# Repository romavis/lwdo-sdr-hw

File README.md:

# What

**LWDO-SDR** is an experimental device for wide-band LF/VLF radio reception and using LF/VLF signals for precise timekeeping and generic DSP/SDR research purposes.

The name LWDO-SDR *(**l**ong-**w**ave **d**isciplined **o**scillator with **s**oftware **d**efined **r**adio)* is a moniker aking to a widely-used *GPSDO* term, but instead of GPS we use signals transmitted within long wave radio band, and SDR for signal processing.

# Goals

LWDO-SDR is built upon following ideas:
- Wide dynamic range capture of the whole LF/VLF radio spectrum (up to 500 KHz)
  - Simultaneous reception of any number of stations
  - Exposing it as a WebSDR (for the fun of it?)
- Precise built-in VCTCXO oscillator
  - Generates tightly controlled ADC sample clock that allows for SDR processing using large-time-constant averaging
  - Digitally-controlled (via 16 bit DAC), and can be disciplined by:
    - External 1 PPS or 1,2,5,10MHz reference (via DPLL)
    - Received radio signals
- Synchronous capture from multiple antennas (up to 4)
  - Experiments with urban noise suppression SDR algorithms 
  - Directional reception (using e.g. two or three loop antennas)
- Raw data streaming over USB High Speed interface, processing on the USB host device (PC, RaspberryPi, etc.)
  - Because we don't want to be limited by computing power of an embedded MCU or DSP
- Single PCB, two form-factors:
  - Standalone, USB bus-powered - for ease of use and portability (uses Hammond 1455P1601 case)
  - Embedded, self-powered - for use within e.g. a standalone clock source unit within the home lab.

Some signals that can be received by LWDO-SDR are:
- [DCF77 - 77.5KHz](https://en.wikipedia.org/wiki/DCF77)
- [MSF - 60 KHz](https://en.wikipedia.org/wiki/Time_from_NPL_(MSF))
- [RBU - 66.67 KHz](https://en.wikipedia.org/wiki/RBU_(radio_station))
- [TDF - 162 KHz](https://en.wikipedia.org/wiki/ALS162_time_signal)
- [Loran - 100 KHz](https://en.wikipedia.org/wiki/Loran-C)

# Drawings

PDF renders:
- [Schematic](./doc/schematic-rev1.0.pdf)
- [PCB visualisation](./doc/pcb-rev1.0.pdf)

Curious ones are kindly asked to look into the original KiCad 6.0.4 CAD files, which include full PCB drawings and BOM information.

Photo of assembled board can be seen [here](./doc/pcb-photo-rev1.0.jpg).

# HW description

### FPGA

The core of the LWDO-SDR is a low-end FPGA - *ICE40HX4K-TQ144* - that has:
- 3520x 4-input LUT, 1 FF logic cells (7680x with Yosys toolchain)
- 20x 4kbit dual-port block RAM cells (32x with Yosys)
- 2x PLLs
- DDR IO cells
- No hardware multipliers
- Typically achievable clock rates of 40~100MHz (depending on the design)

This FPGA has been chosen for its price and hobbyist-friendliness: TQFP144 can be soldered by hand and allows using 2-layer PCB. However, it is rather small so e.g. it may not be possible to use any kind of softCPU there (remains to be seen..). Any kind of sophisticated DSP is also out of the question, since there are no hardware multipliers.

The bitstream together with any extra user data is stored within 2 MByte QSPI flash - *W25Q16JV*.

FPGA is also connected to a 10 ns 512 KByte SRAM with 16 bit data bus - *IS61WV25616FBLL-10TLI*. At this moment it is not clear how much useful the SRAM may be, given overall FPGA footprint constraints.

### USB

USB 2.0 High Speed is implemented by FTDI FT2232H chip. It has two external channels, allocated as follows:
- Channel A - synchronous FIFO - allows data streaming from/to FPGA up to 40 MByte/s over USB bulk endpoints
- Channel B - MPSSE (SPI) + GPIO - to program bitstream SPI flash and handle CRESET, CDONE, and a pair of extra GPIO-like signals from FPGA (similar to how it's done on the [iCEstick](https://www.latticesemi.com/icestick). Available only when channel A is not in use.

### RF front-end

The board features four input channels for RF signals. All channels are the same:
1. 50 ohm DC-terminated SMA connector.
2. SD12C TVS ESD / overvoltage suppressor.
3. 2nd (3rd) order LC LPF (-3dB cutoff circa 530 KHz, rolloff 12 dB/oct).
4. Schottky diode overvoltage protection.
5. THS4521 fully-differential amplifier, performing unbalanced-balanced conversion and connected as a 2nd order LPF (-3dB cutoff circa 460 KHz, rolloff 12 dB/oct).
6. Passive RC LPF providing tank capacitance for driving the ADC (-3dB cutoff circa 1 MHz, rolloff 6 dB/oct)

### ADC

Board uses two [AD7357](https://www.analog.com/media/en/technical-documentation/data-sheets/AD7357.pdf), which is a 2-ch simulatenous-sampling 4.2 MSPS 14 bit SAR ADC. The output from each ADC is 2-bit serial bus. At a max sampling rate of 4.2 MSPS this ADC requires serial clock circa 80 MHz, which is provided by the FPGA.

**Note** to achieve timing closure for FPGA-ADC interface, taking into account propagation delays, setup times of ICE40HX IO cells, and especially AD7357 data valid delay (up to 9 ns), the generated clock is resampled on the FPGA pin:
- ICE40 outputs clock on the SCLK line (pin 15 or 20).
- ICE40 samples SCLK line via the input buffer of pin 20, and feeds that clock to the global clock net.
Compared to simply driving internal clock to the pin, this allows to take "global clock net -> pin output" delay (circa 2.5 ns) out of the timing equation.

### Clock source

[DOT050V-020.0M](http://www.conwin.com/datasheets/tx/tx395.pdf) VCTCXO from Connor-Winfield provides master 20 MHz clock for the FPGA, from which all the other clocks are generated using on-die PLLs.
DOT050V is a highly stable precision oscillator. Notable specs are:
- Factory frequency calibration: ±1 ppm
- Stability vs temperature 0~70 °C: ±50 **ppb**
- Stability vs load, supply voltage: ±20 ppb
- Aging over first year: ±300 ppb
- Voltage control frequency pulling range: at least ±10 ppm
- Comes in a standard 9x14mm SMT package

If needed, DOT050V can be easily replaced by some other, potentially cheaper, 3.3V VCTCXO or VCXO directly or through a simple adapter PCB (or DIY-style: some Kynar wire and hot glue). LWDO-SDR contains buffering circuitry that can accept oscillators with both square wave and (clipped) sine wave output.

The oscillator is voltage-controlled through by means of:
- 16-bit SPI DAC [DAC8551](https://www.ti.com/lit/ds/symlink/dac8551.pdf) driven by SPI master implemented on FPGA.
- DAC Vref provided by [MCP1501](https://ww1.microchip.com/downloads/en/DeviceDoc/20005474E.pdf), powered from filtered, unregulated 5V rail. 
- 1st order passive RC LPF (-3dB cutoff circa 160 Hz).
- Non-inverting buffer using [NCS325](www.onsemi.com/pub/Collateral/NCS325-D.PDF) rail-to-rail low-drift low-offset precision OpAmp.

### External clock input and output

There are two extra SMA connectors: one is for external clock input, one is for clock output from the board.

Clock output provides 1 Vpkpk 50 ohm terminated square wave output, AC or DC coupled (controlled by jumper). Output clock may come from one of two sources:
1. Dedicated FPGA pin.
2. 20 MHz master clock from VCTCXO.
The source is selected via a hardware LVCMOS multiplexer chip, controlled by the FPGA.

External clock input is 50 ohm terminated (above ~3MHz), AC or DC coupled. It is buffered and squared by a chain of unbuffered and buffered LVCMOS inverters, and fed to a dedicated FPGA pin.

**NOTE** clock input circuitry depicted on the schematic is sub-optimal. See "Errata" section below.

### External I/O

To allow LWDO-SDR PCB to be embedded, there's a 20-pin IDC ribbon cable connector which provides:
- 8 bit I/O bus connected to the FPGA:
  - Buffered via unidirectional 74AVC4T245 level translators.
  - Direction control for I/O lines is manual, by soldering/desoldering bridge resistors onto PCB.
  - Wired to a ribbon cable in G-S-G order, impedance-matched to a standard 1.27mm-pitch cable.
- External VDDIO supply for the level translators.
- External 5V supply for powering up the board (instead of using USB VBUS).

### LEDs

Board has 6 red/green bi-LEDs [WP130WCP/2EGW](https://www.kingbrightusa.com/images/catalog/SPEC/WP130WCP-2EGW.pdf):
- 4 for monitoring input status (located next to the input connectors)
- 1 for monitoring system status (located next to the USB)
- 1 hard-wired as a green power LED (located next to the USB)

### PCB

The board itself is 2-layer, designed to be manufacturable by [Eurocircuits](https://www.eurocircuits.com/) PCB Proto service according to Class 5C (0.175mm track, 0.25mm annular ring, 0.25mm smallest final hole).

# Software

The testing of rev 1.0 board is, as of 10 May 2022, currently ongoing. The software development is WIP. Source code of FPGA and host SW will be published on GitHub as soon as I have something ready.

# Errata

### Issue 1 - CLK_IN buffer instability

**Symptom:** when AC-coupled, in absence of input signal, or when input signal is weak or slowly-changing (low frequency sine wave), the output of clock buffer contains a lot of random 0->1, 1->0 transitions.

**Cause:** input buffer, implemented with 2x LVCMOS unbuffered invertors, has very high analog gain (circa 40~50dB). That amplifies all kinds of noise when the input signal is not strong enough. Buffered LVCMOS invertors ampify and square that noise signal even further.

**Solution:** problem can be solved by adding hysteresis (Schmitt-trigger action) to the input buffer. For that, an extra 100K resistor needs to be soldered on top of the PCB per schematic shown below:

[Errata-1-rework-schematic](./doc/errata-issue1-rework.png)

# License

Copyright 2022 Roman Dobrodii

SPDX-License-Identifier: Apache-2.0 WITH SHL-2.1

Licensed under the Solderpad Hardware License v 2.1 (the “License”); you may not
use this work except in compliance with the License, or, at your option, the
Apache License version 2.0. You may obtain a copy of the License at

https://solderpad.org/licenses/SHL-2.1/

Unless required by applicable law or agreed to in writing, any work distributed
under the License is distributed on an “AS IS” BASIS, WITHOUT WARRANTIES OR
CONDITIONS OF ANY KIND, either express or implied. See the License for the
specific language governing permissions and limitations under the License.

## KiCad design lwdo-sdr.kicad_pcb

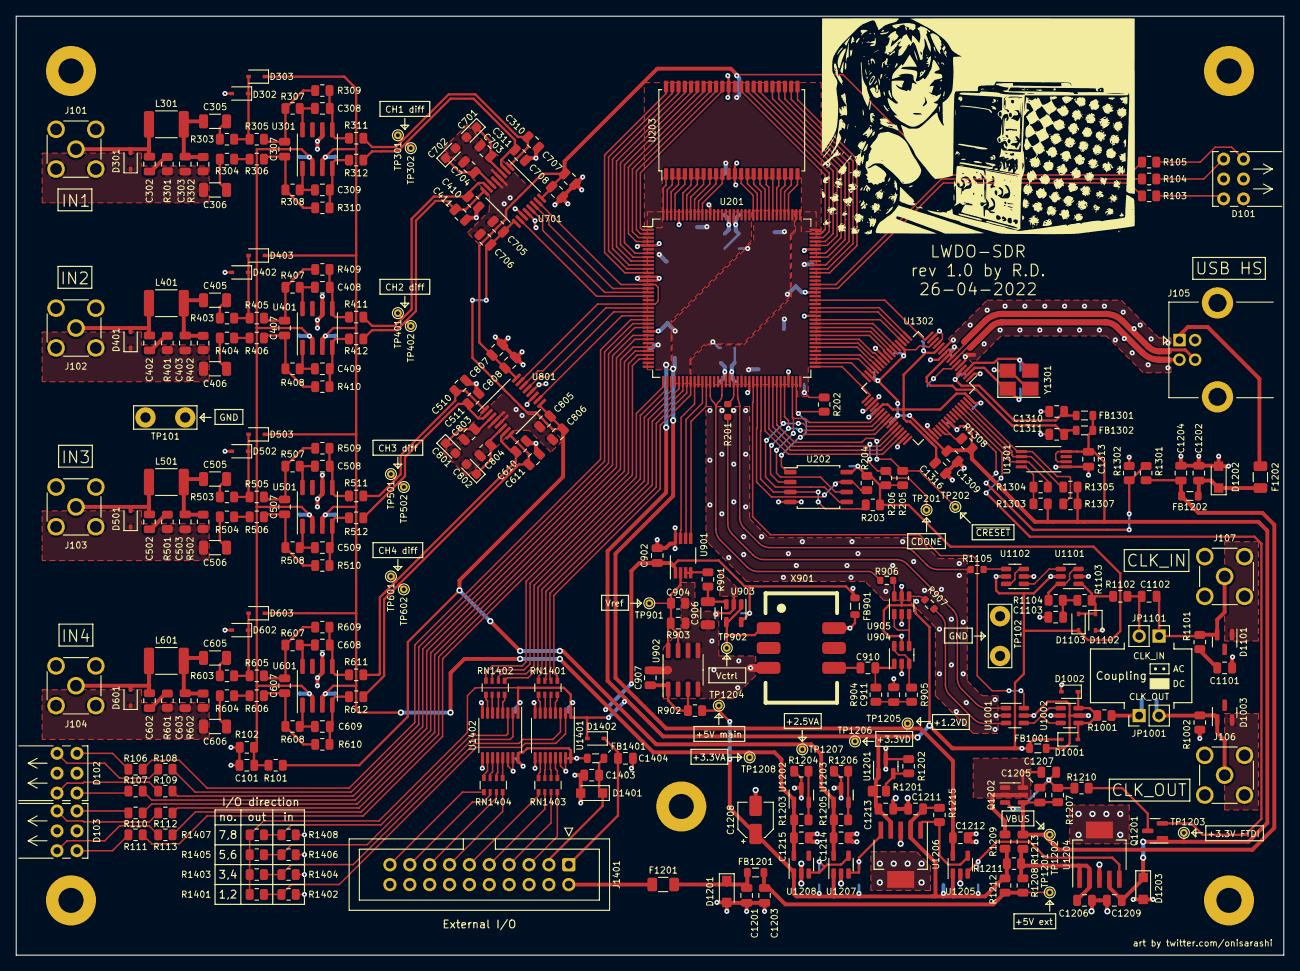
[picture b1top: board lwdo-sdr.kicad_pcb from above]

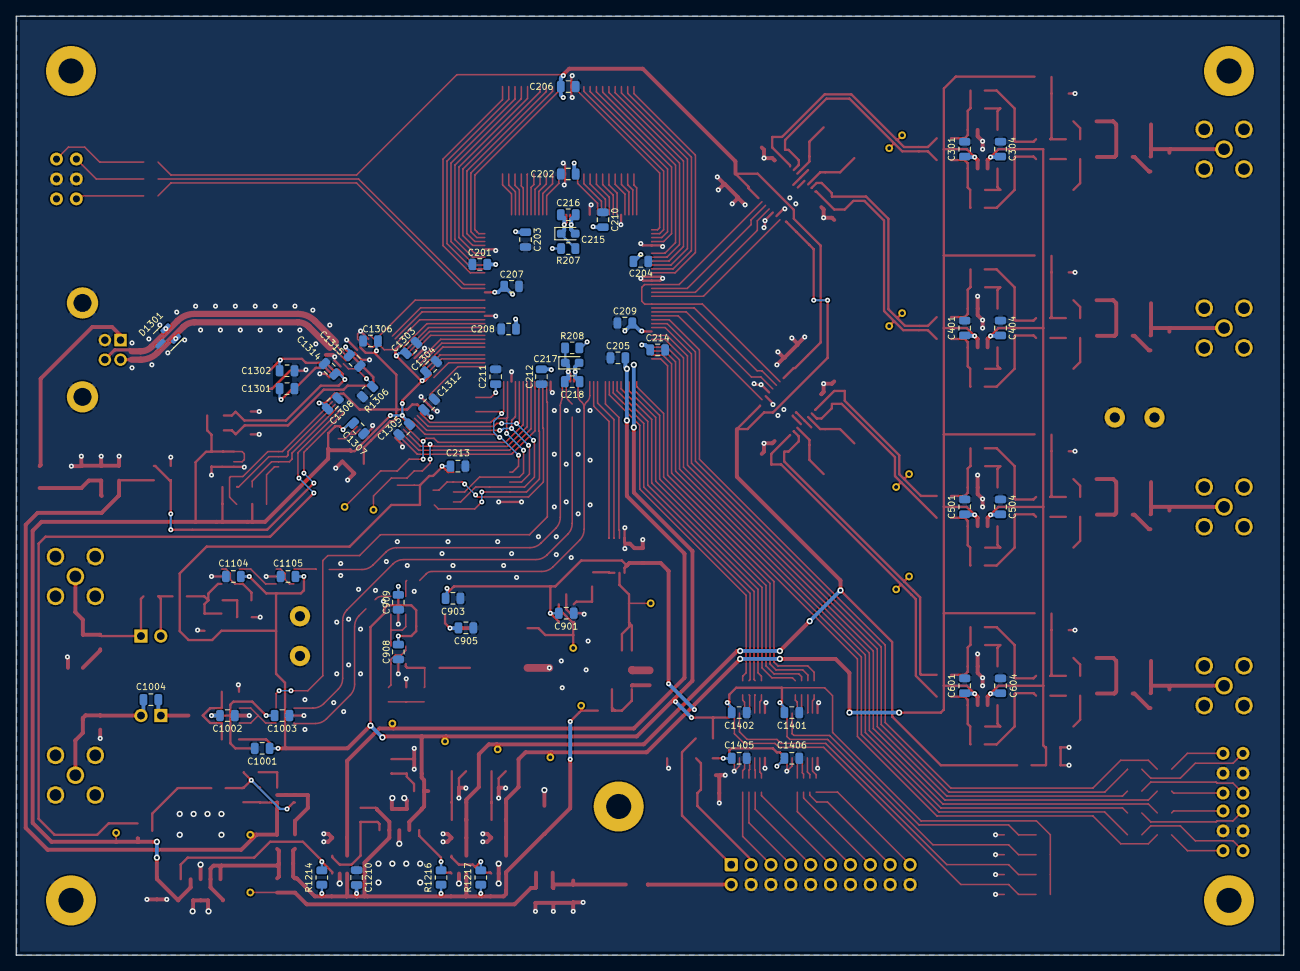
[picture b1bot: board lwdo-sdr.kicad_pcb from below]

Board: 2 copper layers, 162.0 x 120.0 mm, 367 parts (60 on the bottom side), 275 nets.

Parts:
C101, C201, C202, C203, C204, C205, C206, C207, C208, C209, C210, C211, C212, C213, C214, C304, C404, C504, C604, C901, C903, C908, C909, C1001, C1003, C1104, C1105, C1201, C1202, C1203, C1204, C1206, C1209, C1303, C1304, C1305, C1306, C1307, C1308, C1309, C1310, C1311, C1312, C1313, C1314, C1315, C1316, C1401, C1402, C1403, C1404, C1406: 1u; C_0805_2012Metric
C215, C217, C701, C702, C801, C802: 10u; CP_EIA-2012-15_AVX-P
C216, C218, C703, C704, C803, C804, C1004, C1205, C1207: 100n; C_0805_2012Metric
C301, C401, C501, C601, C706, C707, C806, C807, C902, C905, C907, C1002, C1210, C1211, C1212, C1213, C1214, C1215, C1405: 4.7u; C_0805_2012Metric
C302, C303, C402, C403, C502, C503, C602, C603: 6.8n; C_0805_2012Metric
C305, C306, C405, C406, C505, C506, C605, C606, C906: 100n; C_1206_3216Metric
C307, C407, C507, C607, C904, C911, C1102, C1103: 10n; C_0805_2012Metric
C308, C309, C310, C311, C408, C409, C410, C411, C508, C509, C510, C511, C608, C609, C610, C611: 1.5n; C_0805_2012Metric
C705, C708, C805, C808: DNP; C_0805_2012Metric
C910, C1101: 1n; C_0805_2012Metric
C1208: 22u; CP_Elec_4x5.8
C1301, C1302: 27p; C_0805_2012Metric
D101, D102, D103: WP130WCP/2EGW; WP130WCP
D301, D401, D501, D601: SD12C; D_SOD-323
D302, D303, D402, D403, D502, D503, D602, D603, D1001, D1002, D1102, D1103, D1402: BAT54HGW; D_SOD-323
D1003, D1101: PESD5V0X1BT; SOT-23
D1201, D1202: PTVS5V0S1UR; Nexperia_CFP3_SOD-123W
D1203, D1401: PTVS3V3S1UR; Nexperia_CFP3_SOD-123W
D1301: PESD2USB3UV; SOT-23
F1201, F1202: 1206L050/15; Fuse_1206_3216Metric
FB901, FB1001, FB1201, FB1202, FB1301, FB1302, FB1401: 782853701; L_0805_2012Metric
H101, H102, H103, H104, H105: MountingHole_Pad; MountingHole_3.2mm_M3_Pad
J101: IN1; SMA_Molex_73251-2200_Horizontal
J102: IN2; SMA_Molex_73251-2200_Horizontal
J103: IN3; SMA_Molex_73251-2200_Horizontal
J104: IN4; SMA_Molex_73251-2200_Horizontal
J105: USB_B; USB_B_Lumberg_2411_02_Horizontal
J106: CLK_OUT; SMA_Molex_73251-2200_Horizontal
J107: REF_IN; SMA_Molex_73251-2200_Horizontal
J1401: Conn_02x10_Odd_Even; IDC-Header_2x10_P2.54mm_Vertical
JP1001, JP1101: DC; PinHeader_1x02_P2.54mm_Vertical
L301, L401, L501, L601: 18u; L_1812_4532Metric_Pad1.30x3.40mm_HandSolder
Q1201: NX7002AK; SOT-23
Q1202: PMN48XP; SOT-23-6
R101, R102, R1102, R1201, R1203: 1k; R_0805_2012Metric
R103, R104, R105, R106, R107, R108, R109, R110, R111, R112, R113, R309, R310, R409, R410, R509, R510, R609, R610, R1205: 220; R_0805_2012Metric
R201, R906, R907, R1105: 49.9; R_0603_1608Metric
R202, R203, R204, R205, R206, R901, R904, R1103, R1210, R1214, R1215, R1216, R1217, R1302, R1303, R1305, R1307, R1308: 10k; R_0805_2012Metric
R207, R208, R303, R305, R311, R312, R403, R405, R411, R412, R503, R505, R511, R512, R603, R605, R611, R612: 100; R_0805_2012Metric
R301, R401, R501, R601, R902, R1101: 49.9; R_0805_2012Metric
R302, R402, R502, R602: 62; R_0805_2012Metric
R304, R404, R504, R604: 27; R_0805_2012Metric
R306, R406, R506, R606: 200; R_0805_2012Metric
R307, R308, R407, R408, R507, R508, R607, R608: 24; R_0805_2012Metric
R903, R1202, R1204, R1206, R1304: 2.4k; R_0805_2012Metric
R905, R1104, R1207: 100k; R_0805_2012Metric
R1001: 75; R_0805_2012Metric
R1002: 120; R_0805_2012Metric
R1208, R1211, R1212, R1402, R1404, R1406, R1407: DNP; R_0805_2012Metric
R1209, R1213, R1401, R1403, R1405, R1408: 0; R_0805_2012Metric
R1301: 5.1k; R_0805_2012Metric
R1306: 12k; R_0805_2012Metric
RN1401, RN1402, RN1403, RN1404: 4x82R; R_Array_Convex_4x0603
TP101, TP102: TestPoint; TestPoint_Bridge_Pitch5.08mm_Drill1.3mm
TP201, TP202, TP301, TP302, TP401, TP402, TP501, TP502, TP601, TP602, TP901, TP902, TP1201, TP1202, TP1203, TP1204, TP1205, TP1206, TP1207, TP1208: TestPoint; TestPoint_THTPad_D1.0mm_Drill0.5mm
U201: ICE40HX4K; TQFP-144_20x20mm_P0.5mm
U202: W25Q16JV; SOIC-8_5.23x5.23mm_P1.27mm
U203: IS61WV25616FBLL-10TLI; TSOP-II-44_10.16x18.41mm_P0.8mm
U301, U401, U501, U601: THS4521ID; SOIC-8_3.9x4.9mm_P1.27mm
U701, U801: AD7357xRU; TSSOP-16_4.4x5mm_P0.65mm
U901: DAC8551; VSSOP-8_3.0x3.0mm_P0.65mm
U902: MCP1501-33xSN; SOIC-8_3.9x4.9mm_P1.27mm
U903: NCS325; SOT-23-5
U904, U1101: 74LVC2GU04; SOT-23-6
U905, U1002, U1102: 74LVC2G04; SOT-23-6
U1001: 74LVC1G157; SOT-23-6
U1201, U1202, U1203: TL431AFDT; SOT-23
U1204, U1206: MCP1824T-330; SOT-223-6
U1205: NCV8164ASN120T1G; SOT-23-5
U1207: NCV8164ASN250T1G; SOT-23-5
U1208: NCV8164ASN330T1G; SOT-23-5
U1301: AT93C56; TSSOP-8_4.4x3mm_P0.65mm
U1302: FT2232HL; LQFP-64_10x10mm_P0.5mm
U1401, U1402: 74AVC4T245PW; TSSOP-16_4.4x5mm_P0.65mm
X901: DOT050V-020.0M; ConnorWinfield_DOT050
Y1301: 12MHz CL=18p; Crystal_SMD_3225-4Pin_3.2x2.5mm_HandSoldering

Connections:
+1.2VD: C203.1, C205.1, C207.1, C209.1, C1212.1, R207.2, R208.2, TP1205.1, U201.27 (VCC), U201.40 (VCC), U201.92 (VCC), U201.111 (VCC), U1205.5 (Vout)
+2.5VA: C705.1, C706.1, C805.1, C806.1, C1214.1, R101.2, R1205.1, TP1207.1, U701.9 (VDD), U801.9 (VDD), U1203.1 (K), U1207.5 (Vout)
+3.3VA: C301.1, C401.1, C501.1, C601.1, C901.2, C902.2, C903.2, C1215.1, D303.1 (K), D403.1 (K), D503.1 (K), D603.1 (K), FB901.1, R1203.1, TP1208.1, U301.3 (VS+), U401.3 (VS+), U501.3 (VS+), U601.3 (VS+), U901.1 (VDD), U903.5 (V+), U1202.1 (K), U1208.5 (Vout)
+3.3VD: C201.1, C202.1, C204.1, C206.1, C208.1, C210.1, C211.1, C212.1, C213.1, C214.1, C707.1, C708.1, C807.1, C808.1, C908.2, C909.2, C1001.2, C1104.2, C1105.2, C1213.1, C1401.1, C1402.1, D1001.1 (K), D1103.1 (K), D1402.2 (A), FB1001.1, R105.1, R202.1, R203.1, R204.1, R205.1, R206.1, R1201.1, R1401.2, R1403.2, R1405.2, R1407.2, TP1206.1, U201.6 (VCCIO_3), U201.30 (VCCIO_3), U201.46 (VCCIO_2), U201.57 (VCCIO_2), U201.72 (VCC_SPI), U201.89 (VCCIO_1), U201.100 (VCCIO_1), U201.108 (VPP_2V5), U201.123 (VCCIO_0), U201.131 (VCCIO_0), U202.8 (VCC), U203.11 (VDD), U203.33 (VDD), U701.16 (VDRIVE), U801.16 (VDRIVE), U904.5, U905.5, U1101.5, U1102.5, U1201.1 (K), U1206.4 (Vout), U1401.1 (VCCA), U1402.1 (VCCA)
+5VMAIN: C1208.1, C1210.1, C1211.1, R902.2, R1211.2, R1212.1, R1213.2, R1214.2, R1215.2, R1216.2, R1217.2, TP1204.1, U1205.1 (Vin), U1206.2 (Vin), U1207.1 (Vin), U1208.1 (Vin)
/ADC1/ADC.DA: U201.16 (IOL_10B), U701.14 (SDATAA)
/ADC1/ADC.DB: U201.17 (IOL_12A), U701.13 (SDATAB)
/ADC1/ADC.~CS: U201.18 (IOL_12B), U701.10 (~CS)
/ADC1/INA+: C310.1, R311.2, TP301.1, U701.1 (INA+)
/ADC1/INA-: C311.1, R312.2, TP302.1, U701.2 (INA-)
/ADC1/INB+: C411.1, R412.2, TP402.1, U701.8 (INB+)
/ADC1/INB-: C410.1, R411.2, TP401.1, U701.7 (INB-)
/ADC2/ADC.DA: U201.21 (IOL_14A_GBIN6), U801.14 (SDATAA)
/ADC2/ADC.DB: U201.22 (IOL_14B), U801.13 (SDATAB)
/ADC2/ADC.SCK: U201.15 (IOL_10A), U201.20 (IOL_13B_GBIN7), U701.15 (SCLK), U801.15 (SCLK)
/ADC2/ADC.~CS: U201.23 (IOL_17A), U801.10 (~CS)
/ADC2/INA+: C510.1, R511.2, TP501.1, U801.1 (INA+)
/ADC2/INA-: C511.1, R512.2, TP502.1, U801.2 (INA-)
/ADC2/INB+: C611.1, R612.2, TP602.1, U801.8 (INB+)
/ADC2/INB-: C610.1, R611.2, TP601.1, U801.7 (INB-)
/Clock Output/CLK0: R907.2, U1001.3 (A)
/Clock Output/CLK1: R201.1, U1001.1 (B)
/Clock Output/CLK_SEL: U201.60 (IOB_95), U1001.6 (~A/B)
/Clock Output/OUT: C1004.2, D1003.1 (K), J106.1 (In), JP1001.2 (B), R1002.2
/Clock Output/VDD_3V3: C1002.2, C1003.2, FB1001.2, U1001.5, U1002.5
/Extension Connector/5VEXT: F1201.1, J1401.2
/Extension Connector/DIR12: R1401.1, R1402.2, U1401.2 (1DIR)
/Extension Connector/DIR34: R1403.1, R1404.2, U1401.3 (2DIR)
/Extension Connector/DIR56: R1405.1, R1406.2, U1402.2 (1DIR)
/Extension Connector/DIR78: R1407.1, R1408.2, U1402.3 (2DIR)
/Extension Connector/EXT_IO1: J1401.5, RN1403.8 (R1.2)
/Extension Connector/EXT_IO2: J1401.7, RN1403.7 (R2.2)
/Extension Connector/EXT_IO3: J1401.9, RN1403.6 (R3.2)
/Extension Connector/EXT_IO4: J1401.11, RN1403.5 (R4.2)
/Extension Connector/EXT_IO5: J1401.13, RN1404.8 (R1.2)
/Extension Connector/EXT_IO6: J1401.15, RN1404.7 (R2.2)
/Extension Connector/EXT_IO7: J1401.17, RN1404.6 (R3.2)
/Extension Connector/EXT_IO8: J1401.19, RN1404.5 (R4.2)
/Extension Connector/EXT_VDD3V3: C1404.1, D1402.1 (K), J1401.1
/Extension Connector/EXT_VDDIO: C1403.1, D1401.1 (K), FB1401.1, J1401.3
/Extension Connector/IO1: RN1401.1 (R1.1), U201.44 (IOB_72)
/Extension Connector/IO2: RN1401.2 (R2.1), U201.43 (IOB_71)
/Extension Connector/IO3: RN1401.3 (R3.1), U201.42 (IOB_64)
/Extension Connector/IO4: RN1401.4 (R4.1), U201.41 (IOB_63)
/Extension Connector/IO5: RN1402.1 (R1.1), U201.39 (IOB_61)
/Extension Connector/IO6: RN1402.2 (R2.1), U201.38 (IOB_57)
/Extension Connector/IO7: RN1402.3 (R3.1), U201.37 (IOB_56)
/Extension Connector/IO8: RN1402.4 (R4.1), U201.34 (IOL_25B)
/Extension Connector/VDDIO: C1405.1, C1406.1, FB1401.2, U1401.16 (VCCB), U1402.16 (VCCB)
/FPGA/CLK_20MHZ: R906.2, U201.49 (IOB_81_GBIN5), U201.52 (IOB_82_GBIN4)
/FPGA/FIFO.CLKOUT: U201.74 (IOR_110), U1302.32 (ACBUS5)
/FPGA/FIFO.D0: U201.90 (IOR_138), U1302.16 (ADBUS0)
/FPGA/FIFO.D1: U201.88 (IOR_137), U1302.17 (ADBUS1)
/FPGA/FIFO.D2: U201.87 (IOR_136), U1302.18 (ADBUS2)
/FPGA/FIFO.D3: U201.85 (IOR_128), U1302.19 (ADBUS3)
/FPGA/FIFO.D4: U201.84 (IOR_120), U1302.21 (ADBUS4)
/FPGA/FIFO.D5: U201.83 (IOR_119), U1302.22 (ADBUS5)
/FPGA/FIFO.D6: U201.82 (IOR_118), U1302.23 (ADBUS6)
/FPGA/FIFO.D7: U201.81 (IOR_117), U1302.24 (ADBUS7)
/FPGA/FIFO.SIWU: U201.75 (IOR_111), U1302.30 (ACBUS4)
/FPGA/FIFO.~OE: U201.73 (IOR_109), U1302.33 (ACBUS6)
/FPGA/FIFO.~RD: U201.78 (IOR_114), U1302.28 (ACBUS2)
/FPGA/FIFO.~RXF: U201.80 (IOR_116), U1302.26 (ACBUS0)
/FPGA/FIFO.~TXE: U201.79 (IOR_115), U1302.27 (ACBUS1)
/FPGA/FIFO.~WR: U201.76 (IOR_112), U1302.29 (ACBUS3)
/FPGA/FT_IO.CDONE: R206.2, TP201.1, U201.65 (CDONE), U1302.44 (BDBUS5)
/FPGA/FT_IO.IO1: U201.64 (IOB_104_CBSEL1), U1302.45 (BDBUS6)
/FPGA/FT_IO.IO2: U201.63 (IOB_103_CBSEL0), U1302.46 (BDBUS7)
/FPGA/FT_IO.~CRESET: R205.2, TP202.1, U201.66 (~CRESET), U1302.43 (BDBUS4)
/FPGA/FT_SPI.MISO: U201.68 (IOB_106_SDI), U202.2 (DO/IO1), U1302.40 (BDBUS2)
/FPGA/FT_SPI.MOSI: U201.67 (IOB_105_SDO), U202.5 (DI/IO0), U1302.39 (BDBUS1)
/FPGA/FT_SPI.SCK: U201.70 (IOB_107_SCK), U202.6 (CLK), U1302.38 (BDBUS0)
/FPGA/FT_SPI.~CS: R202.2, U201.71 (IOB_108_SS), U202.1 (~CS), U1302.41 (BDBUS3)
/FPGA/LED.IN_G1: R107.1, U201.28 (IOL_23A)
/FPGA/LED.IN_G2: R109.1, U201.26 (IOL_18B)
/FPGA/LED.IN_G3: R111.1, U201.33 (IOL_25A)
/FPGA/LED.IN_G4: R113.1, U201.32 (IOL_24B)
/FPGA/LED.IN_R1: R106.1, U201.24 (IOL_17B)
/FPGA/LED.IN_R2: R108.1, U201.25 (IOL_18A)
/FPGA/LED.IN_R3: R110.1, U201.29 (IOL_23B)
/FPGA/LED.IN_R4: R112.1, U201.31 (IOL_24A)
/FPGA/LED.STS_G: R104.1, U201.94 (IOR_141_GBIN2)
/FPGA/LED.STS_R: R103.1, U201.93 (IOR_140_GBIN3)
/FPGA/QSPI_IO2: R203.2, U201.62 (IOB_102), U202.3 (~WP/IO2)
/FPGA/QSPI_IO3: R204.2, U201.61 (IOB_96), U202.7 (~HOLD/IO3)
/FPGA/REF_CLK_IN: R1105.2, U201.56 (IOB_94)
/FPGA/SRAM.A0: U201.144 (IOT_222), U203.1 (A0)
/FPGA/SRAM.A1: U201.143 (IOT_221), U203.2 (A1)
/FPGA/SRAM.A2: U201.142 (IOT_220), U203.3 (A2)
/FPGA/SRAM.A3: U201.141 (IOT_219), U203.4 (A3)
/FPGA/SRAM.A4: U201.139 (IOT_217), U203.5 (A4)
/FPGA/SRAM.A5: U201.116 (IOT_173), U203.18 (A5)
/FPGA/SRAM.A6: U201.115 (IOT_172), U203.19 (A6)
/FPGA/SRAM.A7: U201.114 (IOT_171), U203.20 (A7)
/FPGA/SRAM.A8: U201.113 (IOT_170), U203.21 (A8)
/FPGA/SRAM.A9: U201.112 (IOT_169), U203.22 (A9)
/FPGA/SRAM.A10: U201.97 (IOR_147), U203.23 (A10)
/FPGA/SRAM.A11: U201.98 (IOR_148), U203.24 (A11)
/FPGA/SRAM.A12: U201.99 (IOR_152), U203.25 (A12)
/FPGA/SRAM.A13: U201.101 (IOR_160), U203.26 (A13)
/FPGA/SRAM.A14: U201.102 (IOR_161), U203.27 (A14)
/FPGA/SRAM.A15: U201.10 (IOL_5B), U203.42 (A15)
/FPGA/SRAM.A16: U201.11 (IOL_8A), U203.43 (A16)
/FPGA/SRAM.A17: U201.12 (IOL_8B), U203.44 (A17)
/FPGA/SRAM.D0: U201.137 (IOT_215), U203.7 (I/O0)
/FPGA/SRAM.D1: U201.136 (IOT_214), U203.8 (I/O1)
/FPGA/SRAM.D2: U201.135 (IOT_213), U203.9 (I/O2)
/FPGA/SRAM.D3: U201.134 (IOT_212), U203.10 (I/O3)
/FPGA/SRAM.D4: U201.121 (IOT_181), U203.13 (I/O4)
/FPGA/SRAM.D5: U201.120 (IOT_179), U203.14 (I/O5)
/FPGA/SRAM.D6: U201.119 (IOT_178), U203.15 (I/O6)
/FPGA/SRAM.D7: U201.118 (IOT_177), U203.16 (I/O7)
/FPGA/SRAM.D8: U201.104 (IOR_164), U203.29 (I/O8)
/FPGA/SRAM.D9: U201.105 (IOR_165), U203.30 (I/O9)
/FPGA/SRAM.D10: U201.106 (IOR_166), U203.31 (I/O10)
/FPGA/SRAM.D11: U201.107 (IOR_167), U203.32 (I/O11)
/FPGA/SRAM.D12: U201.1 (IOL_2A), U203.35 (I/O12)
/FPGA/SRAM.D13: U201.2 (IOL_2B), U203.36 (I/O13)
/FPGA/SRAM.D14: U201.3 (IOL_3A), U203.37 (I/O14)
/FPGA/SRAM.D15: U201.4 (IOL_3B), U203.38 (I/O15)
/FPGA/SRAM.~CS: U201.138 (IOT_216), U203.6 (~CS)
/FPGA/SRAM.~LB: U201.7 (IOL_4A), U203.39 (~LB)
/FPGA/SRAM.~OE: U201.9 (IOL_5A), U203.41 (~OE)
/FPGA/SRAM.~UB: U201.8 (IOL_4B), U203.40 (~UB)
/FPGA/SRAM.~WE: U201.117 (IOT_174), U203.17 (~WE)
/FPGA/VCXO_DAC.DIN: U201.45 (IOB_73), U901.7 (DIN)
/FPGA/VCXO_DAC.SCK: U201.47 (IOB_79), U901.6 (SCLK)
/FPGA/VCXO_DAC.~SYNC: U201.48 (IOB_80), U901.5 (~SYNC)
/FTDI/FT_3V3: C1209.1, C1303.1, C1304.1, C1305.1, C1307.1, C1309.1, C1313.1, D1203.1 (K), FB1301.2, FB1302.2, Q1201.1 (G), R1303.2, R1305.2, R1307.2, R1308.2, TP1203.1, U1204.4 (Vout), U1301.6 (ORG), U1301.8 (VCC), U1302.14 (~RESET), U1302.20 (VCCIO), U1302.31 (VCCIO), U1302.42 (VCCIO), U1302.50 (VREGIN), U1302.56 (VCCIO)
/FTDI/FT_+1V8: C1306.1, C1308.1, C1312.1, C1316.1, U1302.12 (VCORE), U1302.37 (VCORE), U1302.49 (VREGOUT), U1302.64 (VCORE)
/FTDI/FT_VPHY: C1310.1, C1314.1, FB1301.1, U1302.4 (VPHY)
/FTDI/FT_VPLL: C1311.1, C1315.1, FB1302.1, U1302.9 (VPLL)
/FTDI/USB_D+: D1301.2 (K), J105.3 (D+), U1302.8 (DP)
/FTDI/USB_D-: D1301.1 (K), J105.2 (D-), U1302.7 (DM)
/FTDI/~PWREN: Q1201.2 (S), U1302.60 (~PWREN)
/FTDI/~PWRSAV: R1301.1, R1302.2, U1302.59 (BCBUS7)
/Input Amplifier 1/IN: C302.1, D301.2 (A2), J101.1 (In), L301.1
/Input Amplifier 1/VOCM: C101.2, C304.1, C404.1, C504.1, C604.1, R101.1, R102.2, U301.2 (VOCM), U401.2 (VOCM), U501.2 (VOCM), U601.2 (VOCM)
/Input Amplifier 2/IN: C402.1, D401.2 (A2), J102.1 (In), L401.1
/Input Amplifier 3/IN: C502.1, D501.2 (A2), J103.1 (In), L501.1
/Input Amplifier 4/IN: C602.1, D601.2 (A2), J104.1 (In), L601.1
/Power Supply/5VEXT_CLEAN: C1203.1, FB1201.1, R1208.1, R1212.2, TP1201.1
/Power Supply/+5VFTDI: C1206.1, R1208.2, R1209.1, R1211.1, U1204.1 (~SHDN), U1204.2 (Vin)
/Power Supply/VBUS: F1202.1, J105.1 (VBUS)
/Power Supply/VBUS_CLEAN: C1204.1, C1205.1, FB1202.1, Q1202.4 (S), R1207.1, R1209.2, R1301.2, TP1202.1
/Reference Clock Input/IN: C1102.1, D1101.2 (K), J107.1 (In), JP1101.1 (A), R1101.2
/VCXO/VCXO_VCC: C905.2, FB901.2, X901.6 (VCC)
AGND: C101.1, C201.2, C202.2, C203.2, C204.2, C205.2, C206.2, C207.2, C208.2, C209.2, C210.2, C211.2, C212.2, C213.2, C214.2, C301.2, C303.2, C304.2, C306.1, C310.2, C311.2, C401.2, C403.2, C404.2, C406.1, C410.2, C411.2, C501.2, C503.2, C504.2, C506.1, C510.2, C511.2, C601.2, C603.2, C604.2, C606.1, C610.2, C611.2, C701.2, C702.2, C703.2, C704.2, C705.2, C706.2, C707.2, C708.2, C801.2, C802.2, C803.2, C804.2, C805.2, C806.2, C807.2, C808.2, C901.1, C902.1, C903.1, C904.2, C905.1, C906.2, C907.1, C908.1, C909.1, C911.2, C1001.1, C1002.1, C1003.1, C1101.2, C1103.2, C1104.1, C1105.1, C1201.2, C1202.2, C1203.2, C1204.2, C1206.2, C1208.2, C1209.2, C1210.2, C1211.2, C1212.2, C1213.2, C1214.2, C1215.2, C1301.2, C1302.2, C1303.2, C1304.2, C1305.2, C1306.2, C1307.2, C1308.2, C1309.2, C1310.2, C1311.2, C1312.2, C1313.2, C1314.2, C1315.2, C1316.2, C1401.2, C1402.2, C1403.2, C1404.2, C1405.2, C1406.2, D101.2 (K1), D101.5 (K2), D102.2 (K1), D102.5 (K2), D103.2 (K1), D103.5 (K2), D301.1 (A1), D302.2 (A), D401.1 (A1), D402.2 (A), D501.1 (A1), D502.2 (A), D601.1 (A1), D602.2 (A), D1002.2 (A), D1003.2 (K), D1101.1 (K), D1102.2 (A), D1201.2 (A), D1202.2 (A), D1203.2 (A), D1301.3 (A), D1401.2 (A), H101.1, H102.1, J101.2 (Ext), J102.2 (Ext), J103.2 (Ext), J104.2 (Ext), J105.4 (GND), J105.5 (Shield), J106.2 (Ext), J107.2 (Ext), J1401.4, J1401.6, J1401.8, J1401.10, J1401.12, J1401.14, J1401.16, J1401.18, J1401.20, R102.1, R301.2, R302.1, R401.2, R402.1, R501.2, R502.1, R601.2, R602.1, R903.1, R1002.1, R1202.2, R1204.2, R1206.2, R1302.1, R1306.2, R1402.1, R1404.1, R1406.1, R1408.1, TP101.1, TP102.1, U201.5 (GND), U201.13 (GND), U201.14 (GND), U201.59 (GND), U201.69 (GND), U201.86 (GND), U201.103 (GND), U201.132 (GND), U201.140 (GND), U202.4 (GND), U203.12 (GND), U203.34 (GND), U301.6 (VS-), U401.6 (VS-), U501.6 (VS-), U601.6 (VS-), U701.4 (REFGND), U701.5 (AGND), U701.11 (AGND), U701.12 (DGND), U801.4 (REFGND), U801.5 (AGND), U801.11 (AGND), U801.12 (DGND), U901.8 (GND), U902.2 (GND), U902.4 (GND), U902.5 (GND), U902.6 (GND), U903.2 (V-), U904.2, U905.2, U1001.2, U1002.2, U1101.2, U1102.2, U1201.3 (A), U1202.3 (A), U1203.3 (A), U1204.3 (GND), U1204.6 (GND), U1205.2 (GND), U1206.3 (GND), U1206.6 (GND), U1207.2 (GND), U1208.2 (GND), U1301.5 (GND), U1302.1 (GND), U1302.5 (GND), U1302.10 (AGND), U1302.11 (GND), U1302.13 (TEST), U1302.15 (GND), U1302.25 (GND), U1302.35 (GND), U1302.47 (GND), U1302.51 (GND), U1401.8 (GND), U1401.9 (GND), U1401.14 (2~OE), U1401.15 (1~OE), U1402.8 (GND), U1402.9 (GND), U1402.14 (2~OE), U1402.15 (1~OE), X901.3 (GND), Y1301.2, Y1301.4
unnamed: C215.1, C216.1, R207.1, U201.126 (VCCPLL1)
unnamed: C215.2, C216.2, U201.127 (GNDPLL1)
unnamed: C217.1, C218.1, R208.1, U201.54 (VCCPLL0)
unnamed: C217.2, C218.2, U201.53 (GNDPLL0)
unnamed: C302.2, R301.1
unnamed: C303.1, C305.1, L301.2, R302.2
unnamed: C305.2, R303.1
unnamed: C306.2, R304.1
unnamed: C307.1, R306.2, R308.1, R310.1
unnamed: C307.2, R305.2, R307.1, R309.1
unnamed: C308.1, R309.2, R311.1, U301.5 (OUT-)
unnamed: C308.2, R307.2, U301.8 (IN+)
unnamed: C309.1, R310.2, R312.1, U301.4 (OUT+)
unnamed: C309.2, R308.2, U301.1 (IN-)
unnamed: C402.2, R401.1
unnamed: C403.1, C405.1, L401.2, R402.2
unnamed: C405.2, R403.1
unnamed: C406.2, R404.1
unnamed: C407.1, R406.2, R408.1, R410.1
unnamed: C407.2, R405.2, R407.1, R409.1
unnamed: C408.1, R409.2, R411.1, U401.5 (OUT-)
unnamed: C408.2, R407.2, U401.8 (IN+)
unnamed: C409.1, R410.2, R412.1, U401.4 (OUT+)
unnamed: C409.2, R408.2, U401.1 (IN-)
unnamed: C502.2, R501.1
unnamed: C503.1, C505.1, L501.2, R502.2
unnamed: C505.2, R503.1
unnamed: C506.2, R504.1
unnamed: C507.1, R506.2, R508.1, R510.1
unnamed: C507.2, R505.2, R507.1, R509.1
unnamed: C508.1, R509.2, R511.1, U501.5 (OUT-)
unnamed: C508.2, R507.2, U501.8 (IN+)
unnamed: C509.1, R510.2, R512.1, U501.4 (OUT+)
unnamed: C509.2, R508.2, U501.1 (IN-)
unnamed: C602.2, R601.1
unnamed: C603.1, C605.1, L601.2, R602.2
unnamed: C605.2, R603.1
unnamed: C606.2, R604.1
unnamed: C607.1, R606.2, R608.1, R610.1
unnamed: C607.2, R605.2, R607.1, R609.1
unnamed: C608.1, R609.2, R611.1, U601.5 (OUT-)
unnamed: C608.2, R607.2, U601.8 (IN+)
unnamed: C609.1, R610.2, R612.1, U601.4 (OUT+)
unnamed: C609.2, R608.2, U601.1 (IN-)
unnamed: C701.1, C703.1, U701.3 (REFA)
unnamed: C702.1, C704.1, U701.6 (REFB)
unnamed: C801.1, C803.1, U801.3 (REFA)
unnamed: C802.1, C804.1, U801.6 (REFB)
unnamed: C904.1, R903.2, TP901.1, U901.2 (VREF), U902.7 (OUT), U902.8 (FB)
unnamed: C906.1, R901.2, U903.3 (+)
unnamed: C907.2, R902.1, U902.1 (VDD), U902.3 (~SHDN)
unnamed: C910.1, R904.1, U904.1
unnamed: C910.2, X901.4 (OUT)
unnamed: C911.1, R904.2, R905.1
unnamed: C1004.1, JP1001.1 (A), R1001.1
unnamed: C1101.1, R1101.1
unnamed: C1102.2, JP1101.2 (B), R1102.2
unnamed: C1103.1, R1103.2, R1104.2
unnamed: C1201.1, D1201.1 (K), F1201.2, FB1201.2
unnamed: C1202.1, D1202.1 (K), F1202.2, FB1202.2
unnamed: C1205.2, C1207.2, Q1202.3 (G), R1207.2, R1210.1
unnamed: C1207.1, Q1202.1 (D), Q1202.2 (D), Q1202.5 (D), Q1202.6 (D), R1213.1
unnamed: C1301.1, U1302.2 (OSCI), Y1301.1
unnamed: C1302.1, U1302.3 (OSCO), Y1301.3
unnamed: D101.1 (A11), R103.2
unnamed: D101.3 (A12), R104.2
unnamed: D101.6 (A22), R105.2
unnamed: D102.1 (A11), R106.2
unnamed: D102.3 (A12), R107.2
unnamed: D102.4 (A21), R108.2
unnamed: D102.6 (A22), R109.2
unnamed: D103.1 (A11), R110.2
unnamed: D103.3 (A12), R111.2
unnamed: D103.4 (A21), R112.2
unnamed: D103.6 (A22), R113.2
unnamed: D302.1 (K), D303.2 (A), R303.2, R305.1
unnamed: D402.1 (K), D403.2 (A), R403.2, R405.1
unnamed: D502.1 (K), D503.2 (A), R503.2, R505.1
unnamed: D602.1 (K), D603.2 (A), R603.2, R605.1
unnamed: D1001.2 (A), D1002.1 (K), R1001.2, U1002.4, U1002.6
unnamed: D1102.1 (K), D1103.2 (A), R1102.1, R1103.1, U1101.1
unnamed: Q1201.3 (D), R1210.2
unnamed: R201.2, U201.55 (IOB_91)
unnamed: R304.2, R306.1
unnamed: R404.2, R406.1
unnamed: R504.2, R506.1
unnamed: R604.2, R606.1
unnamed: R901.1, U901.3 (VFB), U901.4 (VOUT)
unnamed: R905.2, U904.3, U904.6
unnamed: R906.1, U905.6
unnamed: R907.1, U905.4
unnamed: R1104.1, U1101.3, U1101.6
unnamed: R1105.1, U1102.4
unnamed: R1201.2, R1202.1, U1201.2 (REF)
unnamed: R1203.2, R1204.1, U1202.2 (REF)
unnamed: R1205.2, R1206.1, U1203.2 (REF)
unnamed: R1214.1, U1204.5 (PWRGD), U1205.3 (EN)
unnamed: R1215.1, U1205.4 (PWRGD), U1206.1 (~SHDN)
unnamed: R1216.1, U1206.5 (PWRGD), U1207.3 (EN)
unnamed: R1217.1, U1207.4 (PWRGD), U1208.3 (EN)
unnamed: R1303.1, R1304.2, U1301.4 (DO)
unnamed: R1304.1, U1301.3 (DI), U1302.61 (EEDATA)
unnamed: R1305.1, U1301.2 (SCLK), U1302.62 (EECLK)
unnamed: R1306.1, U1302.6 (REF)
unnamed: R1307.1, U1301.1 (CS), U1302.63 (EECS)
unnamed: R1308.1, U1302.53 (BCBUS2), U1302.54 (BCBUS3)
unnamed: RN1401.5 (R4.2), U1401.7 (2A2)
unnamed: RN1401.6 (R3.2), U1401.6 (2A1)
unnamed: RN1401.7 (R2.2), U1401.5 (1A2)
unnamed: RN1401.8 (R1.2), U1401.4 (1A1)
unnamed: RN1402.5 (R4.2), U1402.7 (2A2)
unnamed: RN1402.6 (R3.2), U1402.6 (2A1)
unnamed: RN1402.7 (R2.2), U1402.5 (1A2)
unnamed: RN1402.8 (R1.2), U1402.4 (1A1)
unnamed: RN1403.1 (R1.1), U1401.13 (1B1)
unnamed: RN1403.2 (R2.1), U1401.12 (1B2)
unnamed: RN1403.3 (R3.1), U1401.11 (2B1)
unnamed: RN1403.4 (R4.1), U1401.10 (2B2)
unnamed: RN1404.1 (R1.1), U1402.13 (1B1)
unnamed: RN1404.2 (R2.1), U1402.12 (1B2)
unnamed: RN1404.3 (R3.1), U1402.11 (2B1)
unnamed: RN1404.4 (R4.1), U1402.10 (2B2)
unnamed: TP902.1, U903.1, U903.4 (-), X901.1 (Vcon)
unnamed: U904.4, U905.1, U905.3
unnamed: U1001.4 (Y), U1002.1, U1002.3
unnamed: U1101.4, U1102.1
unnamed: U1102.3, U1102.6

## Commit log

2022-01-25 First commit: some sketches of analog frontend schematic
2022-02-03 Update: slowly drawing schematic
2022-02-06 Schematic: added VCTCXO, clk out, ref in, separated power supply into a new sheet
2022-02-09 Schematic updated
2022-02-14 Schematic sketching done
2022-02-15 Update schematic layout, separate into sheets
2022-02-16 Schematic update
2022-02-20 Schematic: better LDO output capacitor selection, clarified BOM
2022-02-20 Schematic: yet another update -Improve way caps are specified once again -Update cap voltages based on ESD simulation -Make anti-aliasing LC filter more practical - with much less inductors -Specify 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
2022-02-20 Schematic: change mosfets in VBUS switcher
2022-02-20 Schematic: change order of level indicator LEDs from 1-3-2-4 to 1-2-3-4
2022-02-20 Schematic: add PNs for resistors
2022-04-03 Combined update (kicad 6.0.4..) - Update schematic to kicad 6.0.4 - Assign footprints for SMA connectors - Replace MCP1825T with MCP1824T (chip shortages..)
2022-04-06 Replace TL431PK (sot89) with TL431AFDT (sot23)
    - Fix tl431 value & footprint (kicad 6.0.4 bug)
2022-04-06 Remove unused schematic file
2022-04-06 Add DOT050 VCTCXO footprint
2022-04-06 Add Kingbright WP130WCP footprint
2022-04-06 Assign WP130WCP and DTO050 footprints in schematic
2022-04-06 Add 3v3 TVS to extconn VDD supply rail
2022-04-06 PN list: replace PTVSxxS1UTR with PTVSxxS1UR
2022-04-06 Schematic: add mounting holes
2022-04-06 Add and use Superbat SMA connector footprint
2022-04-07 Schematic: reconnect SRAM to ease PCB routing
2022-04-07 Update footprints: - SOD323F, SOD323, SOD123W... intead of generic handsolder version - 3225 xtal - use handsolder footprint - do not use handsolder version for ferrite beads - use SOT-23-6 instead o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
2022-04-08 Add two GND testpoints to the schematic
2022-04-08 PCB: begin layout - Board edge - Al extrusion clearances - Mounting holes - Connectors - FPGA-SRAM A/D buses
2022-04-19 Redesign VOCM network, power FDA from 3v3 directly
2022-04-19 Reconnect some things to simplify PCB routing
2022-04-19 Fix footprints, values and PNs
2022-04-19 FTDI: add extra decoupling
2022-04-19 Power supply: add +5VFTDI net, prettify net names
2022-04-19 Extconn: remove redundant 100n cap
2022-04-19 Power supply rework - Only fixed power source selection via 0ohm jumpers - Make it simpler
2022-04-19 PCB: WIP
2022-04-19 FPGA: swap QSPI pins
2022-04-19 Rename USB dp,dm to d+,d- to make pcbnew happy
2022-04-19 74lvc2g04: swap units
2022-04-19 Replace 10uf al-elco by tantalum -Space savings (0805 vs 4mm cylinder)
2022-04-19 ExtConn: fix bug in net naming
2022-04-19 FPGA: connect LEDs differently
2022-04-19 FT2232H: pull BCBUS2&3 high
2022-04-20 FPGA: remove support for SPI slave mode - Now FTDI can only talk to QSPI flash - FPGA boots exclusively from QSPI flash
2022-04-20 PCB: WIP - Power supply almost laid out
2022-04-21 FPGA: swap CLK_OUT and CLK_SEL
2022-04-22 VCXO: remove Taitien vctcxo, add extra decoupling
2022-04-22 VCXO, REF_IN: add reflection damping resistors
2022-04-23 extconn: add 3v3d output
2022-04-24 PCB: WIP Schematic: minor changes (decoupling, logic element ordering)
2022-04-25 Update schematic: - Redesign of decoupling based on swcad modelling (predominantly use 1uf, no paralleled caps) - Reroute REF_CLK_IN, CLK_SEL net to different FPGA pins - Some net renaming - Ext conn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
2022-04-25 PCB: enable fillets for some zones, fix DRC errors
2022-04-25 PCB: top silkscreen done
2022-04-25 PCB: add silkscreen artwork + revision - Artwork by https://twitter.com/onisarashi/status/1423701946305847296
2022-04-25 PCB: place bottom silkscreen - DRC passing except for some known silkscreen overlaps
2022-04-26 Use standard Molex 73251-2201 footprint for SMA
2022-04-26 PCB: update attribution
2022-04-26 PCB: reroute CLK_20MHZ trace
2022-04-26 PCB: improve FPGA/SRAM power routing (use zones)
2022-04-26 PCB: silkscreen improvement
2022-04-27 - Add matching / anti-ring resistors to clock nets - Use 0603 resistors for anti-ring - Improve CLK_OUT routing
2022-04-27 PCB: minor fix for footprints - no more DRC warnings
2022-04-27 Redesign FDA input overload protection
2022-04-28 Add testpoints for CDONE and CRESET
2022-04-28 Fix: correct BAT54 PN and package - SOD323 not SOD323F
2022-04-28 - Replace 0.18 track by 0.2 (0.18 used by mistake) - Prepare fabrication outputs (don't know why does kicad change a lot of values in PCB file here?)
2022-05-13 Add schematic and pcb plots in PDF
2022-05-13 Add README
